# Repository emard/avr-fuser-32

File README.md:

# AVR-Fuser 32

3-in-1 Resurrector programmer for AVR chips

    HVPP: High-Voltage Parallel Programmer
    HVSP: High-Voltage Serial Programmer
    ISP:  In-System Programmer (SPI)

Based on [AVR-Doper](https://www.obdev.at/products/vusb/avrdoper.html)
firmware running on ATMEGA32 in DIP-40 socket.

AVRDUDE compatible, USB powered, onboard 5V->12V converter,
10-pin ISP header, 20-pin HVPP/HVSP header and 
adapter PCB for many popular DIP packages.

Quick mode without PC and avrdude: Pushbutton
erases chip to factory default state.

Complete with firmware, bootloader, kicad schematics and PCB 
for the programmer and sockets adapter.

Supported devices (I tried many but not all of them :)

    ATMEGA 8, 16, 32, 162, 168P, 328P, 16M1, 32M1, 64M1, 8515, 8535
    ATTINY 11, 13, 15, 26, 84, 85, 2313, 4313

# Remark

This is my old project, just uplodaded to github in order
not to get lost, without trying it to compile or open 
since a long time.

May need some fitting for new avr-gcc and kicad 4.x

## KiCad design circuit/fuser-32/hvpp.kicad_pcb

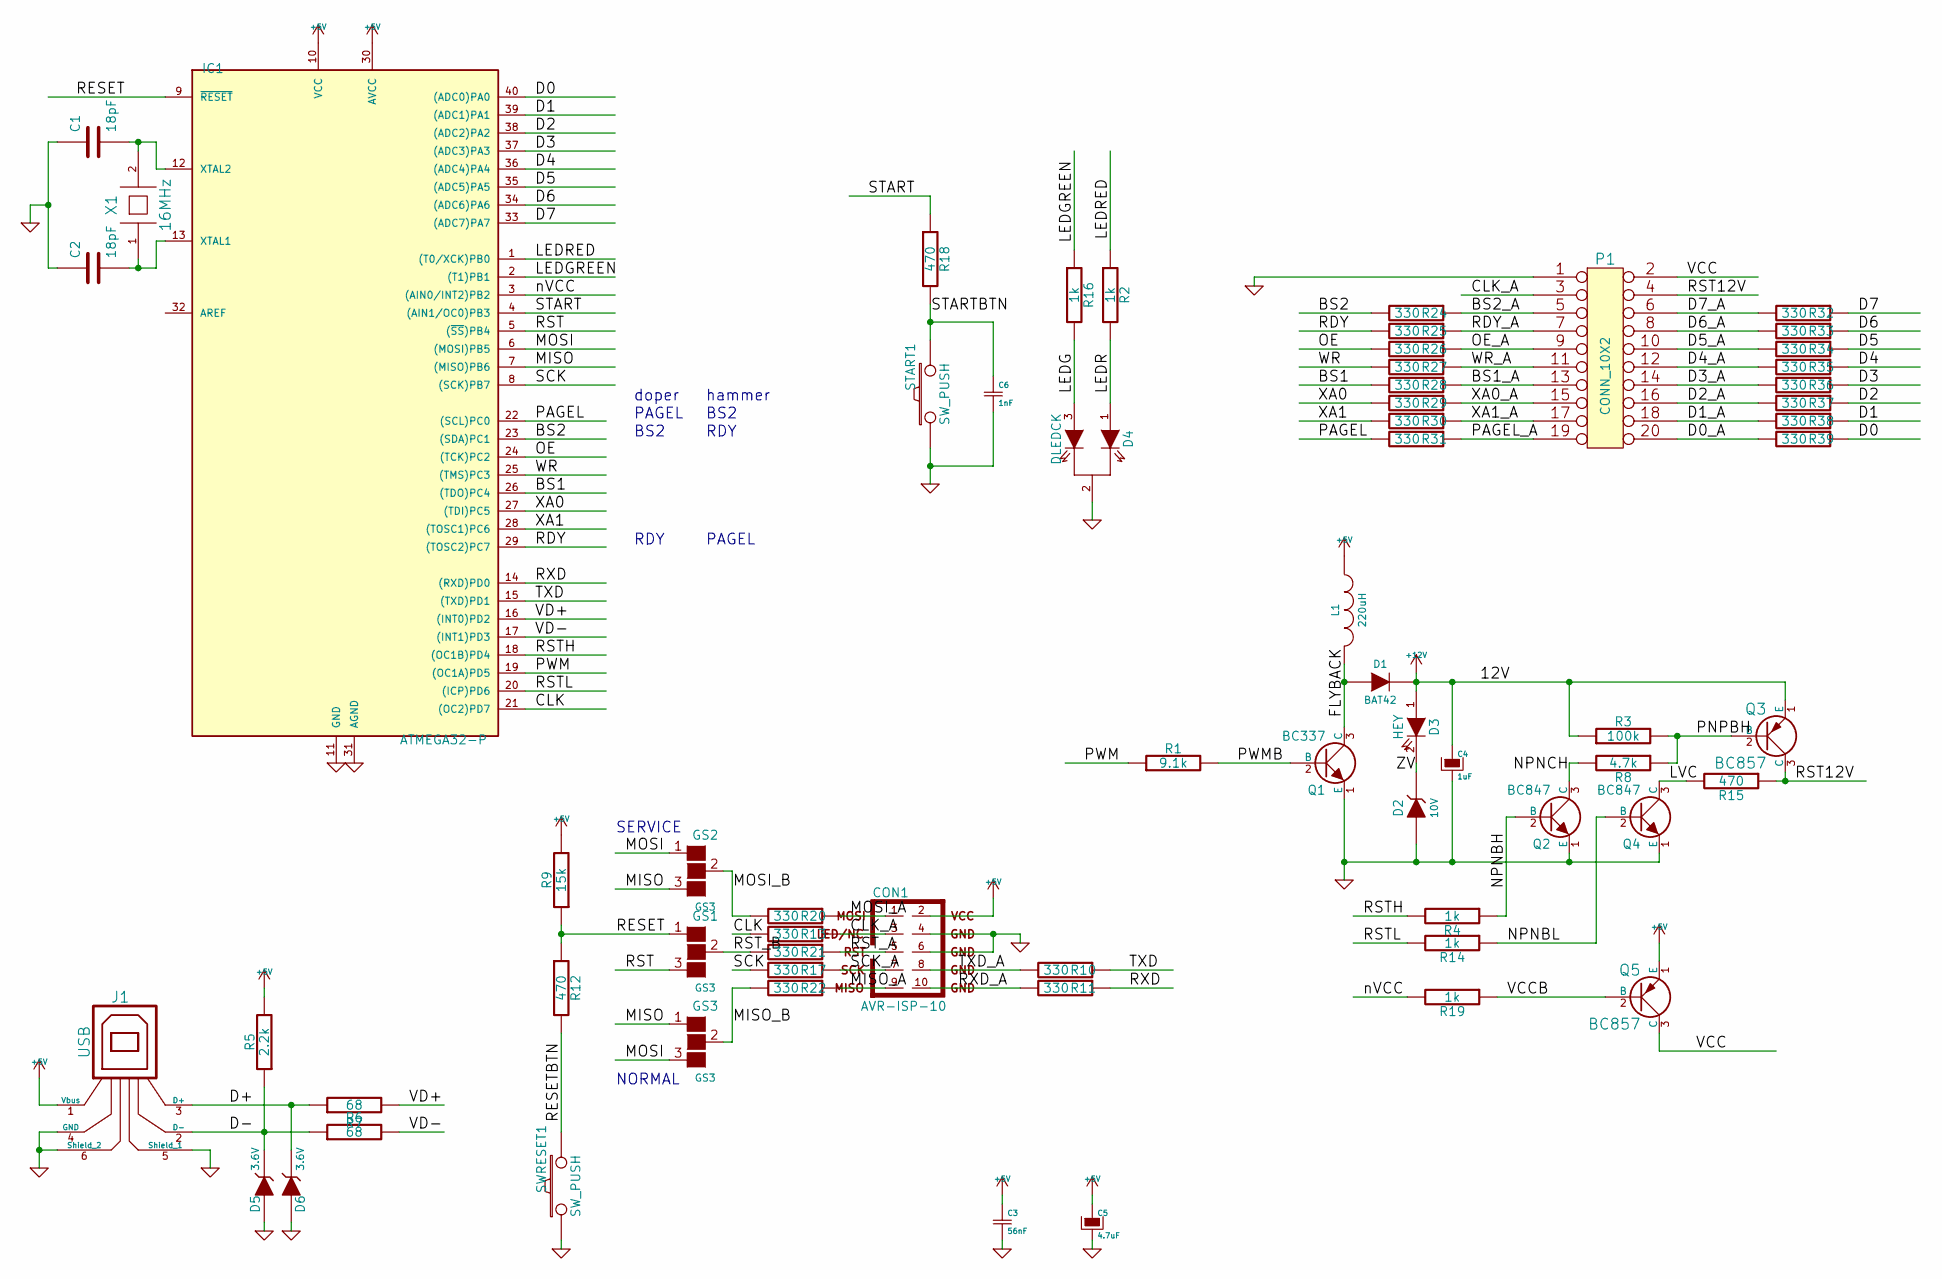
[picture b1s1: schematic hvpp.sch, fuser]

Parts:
C1, C2: 18pF
C3: 56nF
C4: 1uF
C5: 4.7uF
C6: 1nF
CON1: AVR-ISP-10
D1: BAT42
D2: 10V
D3: HEY
D4: DLEDCK
D5, D6: 3.6V
GS1, GS2, GS3: GS3
IC1: ATMEGA32-P; DIL40
J1: USB
L1: 220uH
P1: CONN_10X2
Q1: BC337
Q2, Q4: BC847
Q3, Q5: BC857
R1: 9.1k
R2, R4, R14, R16, R19: 1k
R3: 100k
R5: 2.2k
R6, R7: 68
R8: 4.7k
R9: 15k
R10, R11, R13, R17, R20, R21, R22, R24, R25, R26, R27, R28, R29, R30, R31, R32, R33, R34, R35, R36, R37, R38, R39: 330
R12, R15, R18: 470
START1: SW_PUSH
SWRESET1: SW_PUSH
X1: 16MHz

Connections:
+5V: C3.1, C5.1, CON1.2, IC1.10 (VCC), IC1.30 (AVCC), J1.1 (Vbus), L1.1, Q5.1 (E), R5.2, R9.2
+12V: C4.1, D1.2 (K), D3.1 (A), Q3.1 (E), R3.1
/BS1: IC1.26 ((TDO)PC4), R28.2
/BS1_A: P1.13, R28.1
/BS2: IC1.23 ((SDA)PC1), R24.2
/BS2_A: P1.5, R24.1
/CLK: IC1.21 ((OC2)PD7), R13.2
/CLK_A: CON1.3, P1.3, R13.1
/D0: IC1.40 ((ADC0)PA0), R39.1
/D0_A: P1.20, R39.2
/D1: IC1.39 ((ADC1)PA1), R38.1
/D1_A: P1.18, R38.2
/D2: IC1.38 ((ADC2)PA2), R37.1
/D2_A: P1.16, R37.2
/D3: IC1.37 ((ADC3)PA3), R36.1
/D3_A: P1.14, R36.2
/D4: IC1.36 ((ADC4)PA4), R35.1
/D4_A: P1.12, R35.2
/D5: IC1.35 ((ADC5)PA5), R34.1
/D5_A: P1.10, R34.2
/D6: IC1.34 ((ADC6)PA6), R33.1
/D6_A: P1.8, R33.2
/D7: IC1.33 ((ADC7)PA7), R32.1
/D7_A: P1.6, R32.2
/D+: D6.2 (K), J1.3 (D+), R7.1
/D-: D5.2 (K), J1.2 (D-), R5.1, R6.1
/FLYBACK: D1.1 (A), L1.2, Q1.3 (C)
/LEDG: D4.3 (AGREEN), R16.2
/LEDGREEN: IC1.2 ((T1)PB1), R16.1
/LEDR: D4.1 (ARED), R2.2
/LEDRED: IC1.1 ((T0/XCK)PB0), R2.1
/LVC: Q4.3 (C), R15.2
/MISO: GS2.3 (G3), GS3.1 (G1), IC1.7 ((MISO)PB6)
/MISO_A: CON1.9, R22.1
/MISO_B: GS3.2 (G2), R22.2
/MOSI: GS2.1 (G1), GS3.3 (G3), IC1.6 ((MOSI)PB5)
/MOSI_A: CON1.1, R20.1
/MOSI_B: GS2.2 (G2), R20.2
/NPNBH: Q2.2 (B), R4.1
/NPNBL: Q4.2 (B), R14.1
/NPNCH: Q2.3 (C), R8.2
/OE: IC1.24 ((TCK)PC2), R26.2
/OE_A: P1.9, R26.1
/PAGEL: IC1.22 ((SCL)PC0), R31.2
/PAGEL_A: P1.19, R31.1
/PNPBH: Q3.2 (B), R3.2, R8.1
/PWM: IC1.19 ((OC1A)PD5), R1.1
/PWMB: Q1.2 (B), R1.2
/RDY: IC1.29 ((TOSC2)PC7), R25.2
/RDY_A: P1.7, R25.1
/RESET: GS1.1 (G1), IC1.9 (~RESET), R9.1, R12.1
/RESETBTN: R12.2, SWRESET1.2
/RST: GS1.3 (G3), IC1.5 ((~SS~)PB4)
/RST12V: P1.4, Q3.3 (C), R15.1
/RSTH: IC1.18 ((OC1B)PD4), R4.2
/RSTL: IC1.20 ((ICP)PD6), R14.2
/RST_A: CON1.5, R21.1
/RST_B: GS1.2 (G2), R21.2
/RXD: IC1.14 ((RXD)PD0), R11.1
/RXD_A: CON1.10, R11.2
/SCK: IC1.8 ((SCK)PB7), R17.2
/SCK_A: CON1.7, R17.1
/START: IC1.4 ((AIN1/OC0)PB3), R18.1
/STARTBTN: C6.1, R18.2, START1.2
/TXD: IC1.15 ((TXD)PD1), R10.1
/TXD_A: CON1.8, R10.2
/VCC: P1.2, Q5.3 (C)
/VCCB: Q5.2 (B), R19.1
/VD+: IC1.16 ((INT0)PD2), R7.2
/VD-: IC1.17 ((INT1)PD3), R6.2
/WR: IC1.25 ((TMS)PC3), R27.2
/WR_A: P1.11, R27.1
/XA0: IC1.27 ((TDI)PC5), R29.2
/XA0_A: P1.15, R29.1
/XA1: IC1.28 ((TOSC1)PC6), R30.2
/XA1_A: P1.17, R30.1
/ZV: D2.2 (K), D3.2 (K)
/nVCC: IC1.3 ((AIN0/INT2)PB2), R19.2
GND: C1.1, C2.1, C3.2, C4.2, C5.2, C6.2, CON1.4, CON1.6, D2.1 (A), D4.2 (K), D5.1 (A), D6.1 (A), IC1.11 (GND), IC1.31 (AGND), J1.4 (GND), J1.5 (Shield_1), J1.6 (Shield_2), P1.1, Q1.1 (E), Q2.1 (E), Q4.1 (E), START1.1, SWRESET1.1
unnamed: C1.2, IC1.12 (XTAL2), X1.2
unnamed: C2.2, IC1.13 (XTAL1), X1.1

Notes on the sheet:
doper
SERVICE
NORMAL
PAGEL
RDY
BS2
hammer

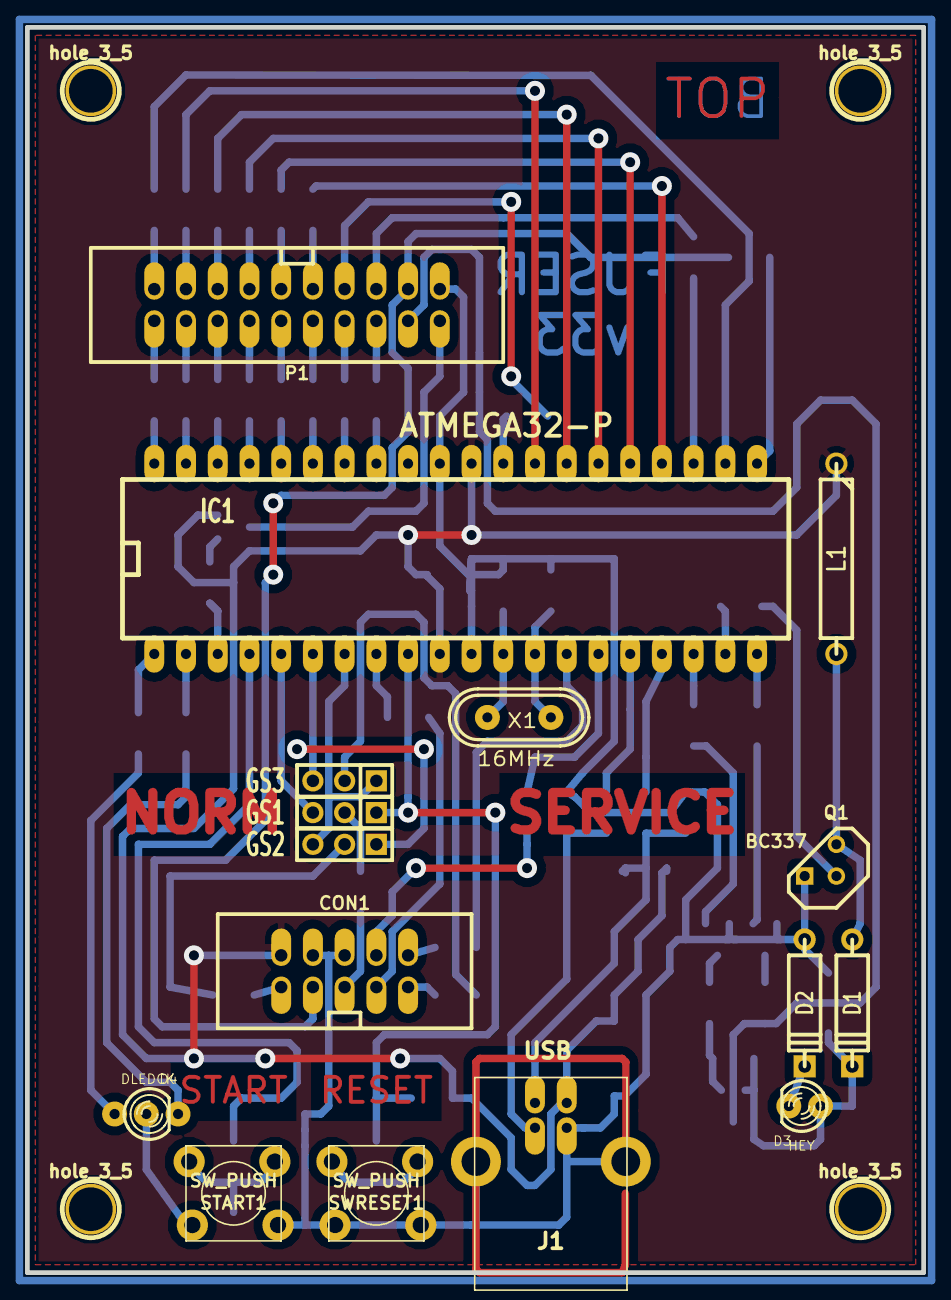
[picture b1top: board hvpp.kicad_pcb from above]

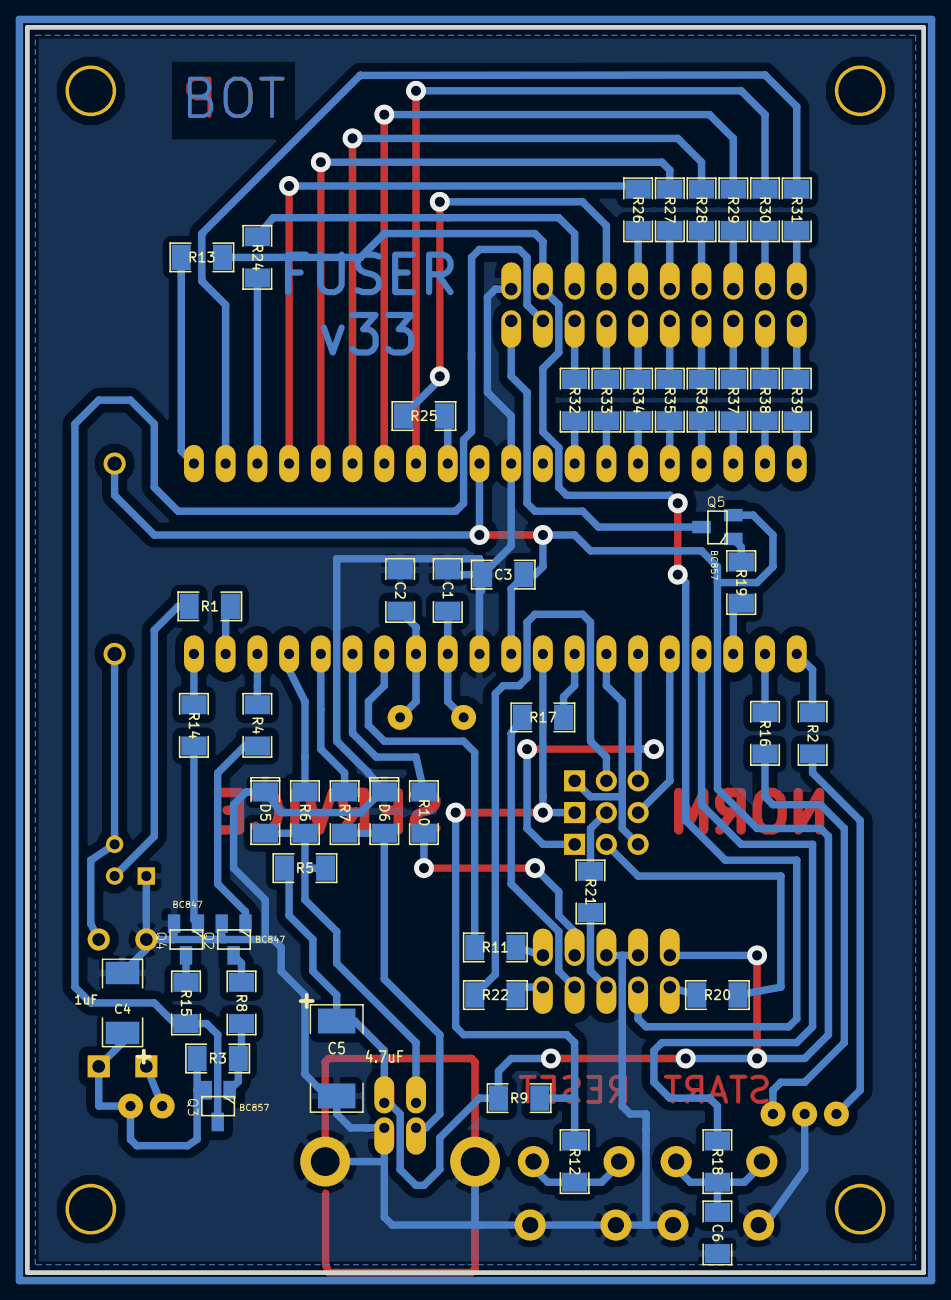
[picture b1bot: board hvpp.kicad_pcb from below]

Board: 2 copper layers, 71.8 x 99.7 mm, 70 parts (50 on the bottom side), 81 nets.

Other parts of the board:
hole_3_5, hole_3_5#2, hole_3_5#3, hole_3_5#4: 3.5mm; hole_3_5

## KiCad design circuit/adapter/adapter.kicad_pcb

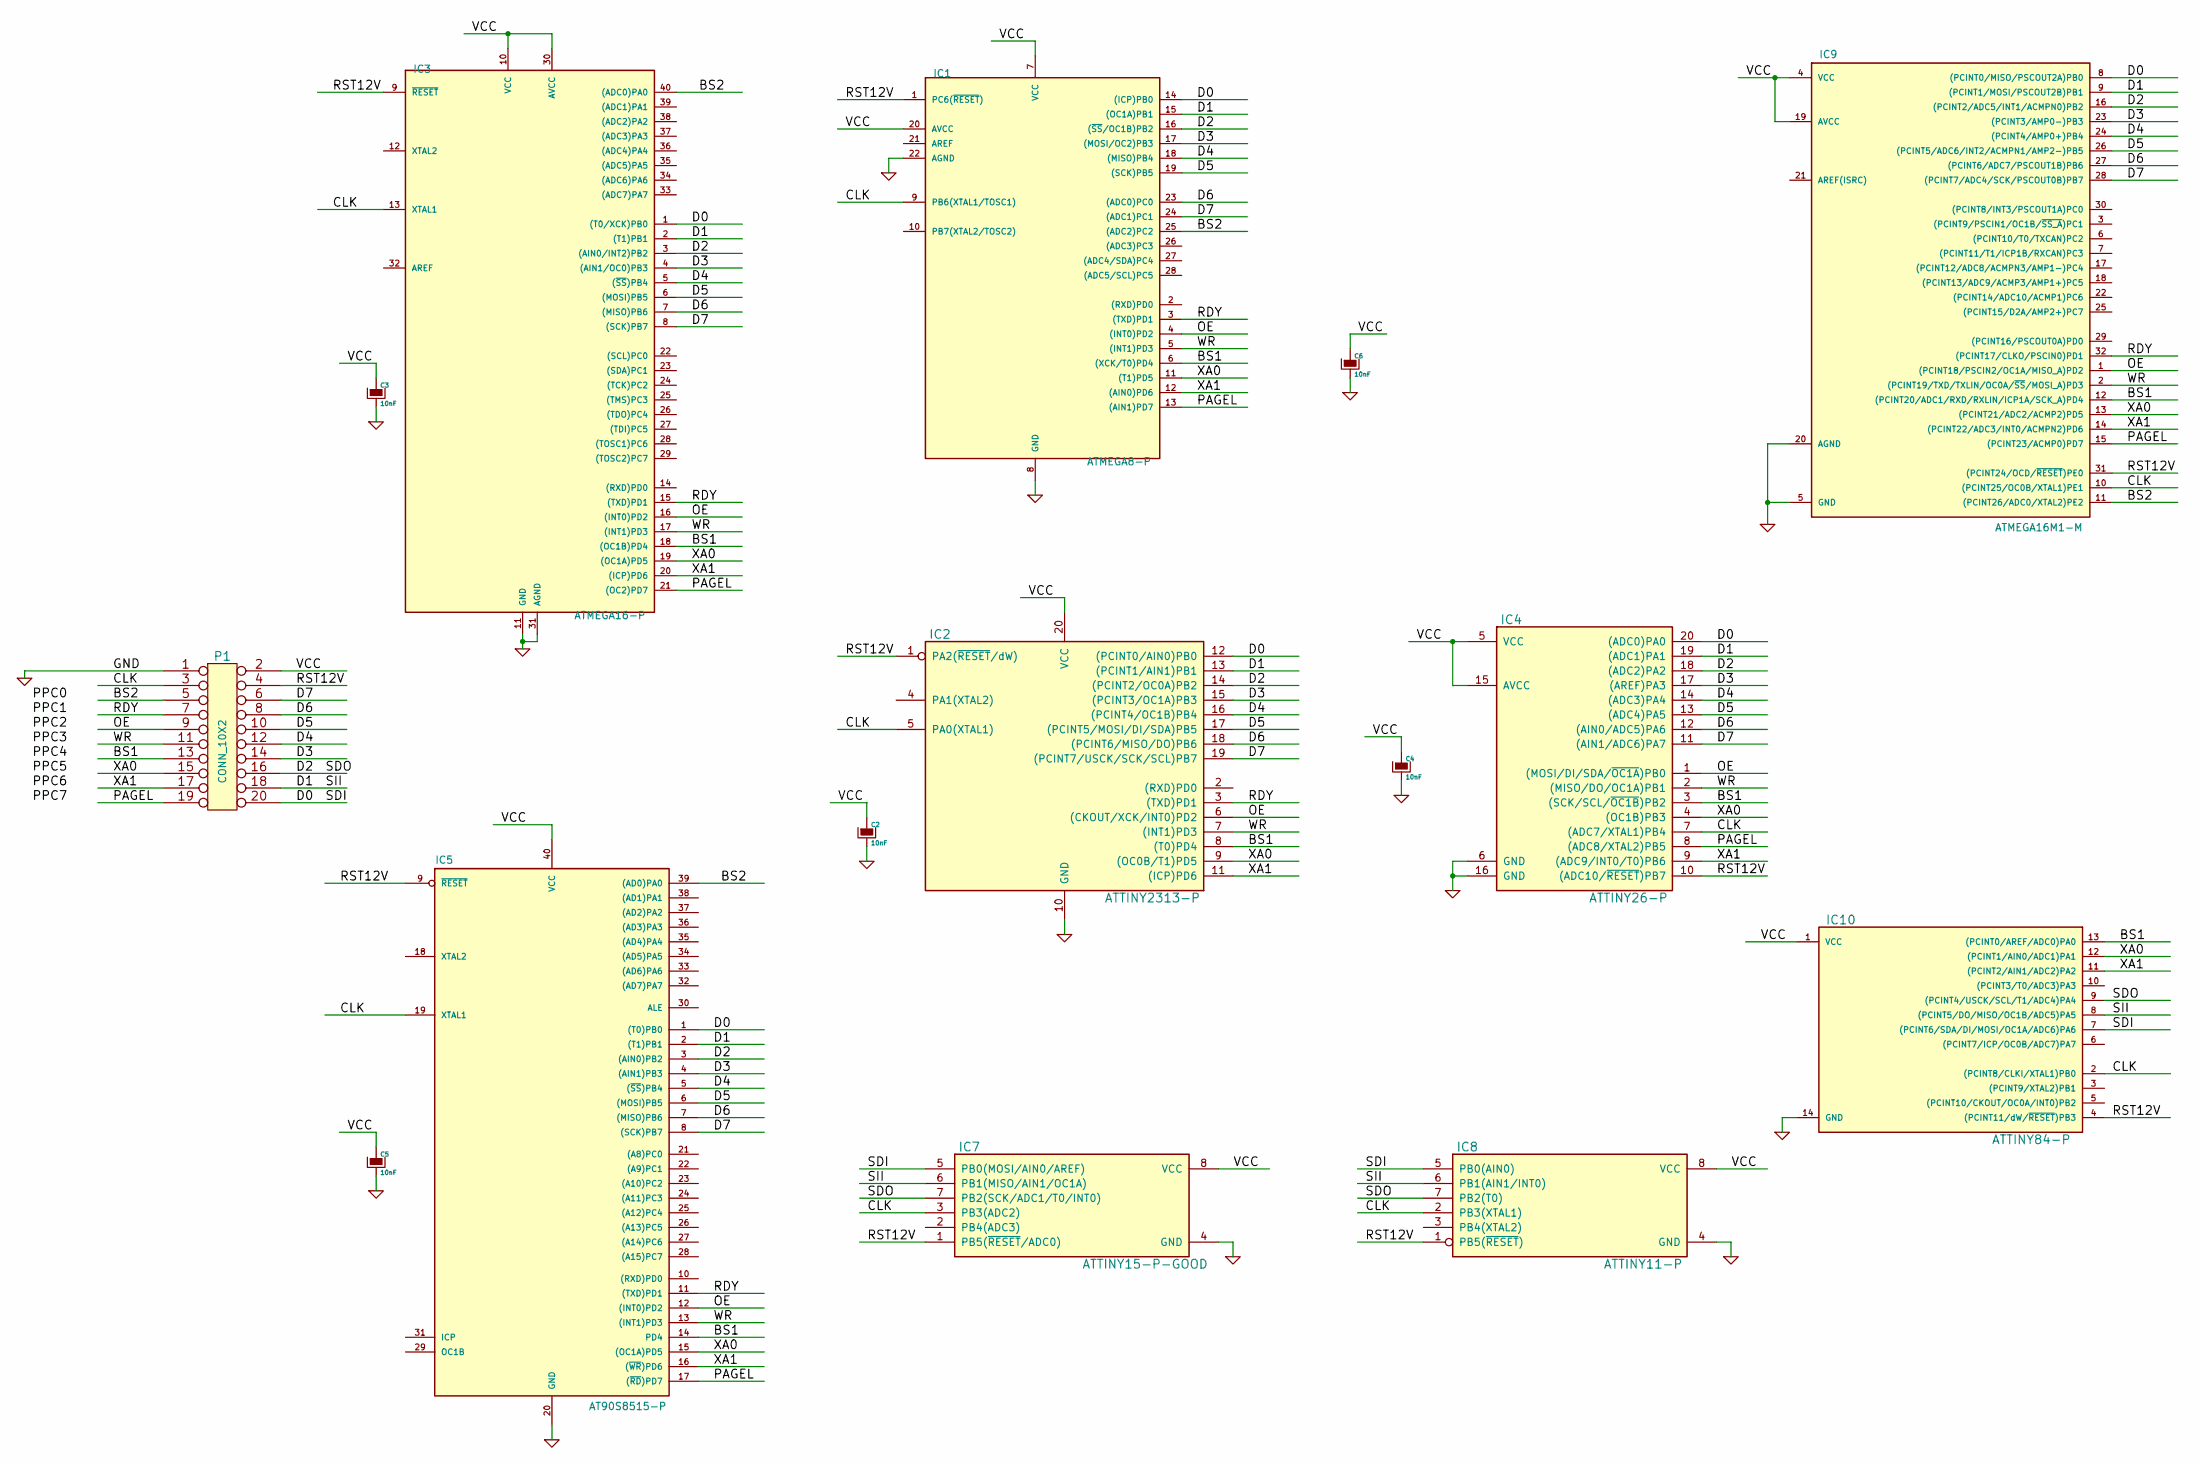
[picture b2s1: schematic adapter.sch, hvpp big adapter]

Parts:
C2, C3, C4, C5, C6: 10nF
IC1: ATMEGA8-P; DIL28
IC2: ATTINY2313-P; DIP20
IC3: ATMEGA16-P; DIL40
IC4: ATTINY26-P; DIP20
IC5: AT90S8515-P; DIL40
IC7: ATTINY15-P-GOOD; DIP8
IC8: ATTINY11-P; DIP8
IC9: ATMEGA16M1-M; QFN32
IC10: ATTINY84-P; DIP14
P1: CONN_10X2

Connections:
/BS1: IC1.6 ((XCK/T0)PD4), IC2.8 ((T0)PD4), IC3.18 ((OC1B)PD4), IC4.3 ((SCK/SCL/~OC1B~)PB2), IC5.14 (PD4), IC9.12 ((PCINT20/ADC1/RXD/RXLIN/ICP1A/SCK_A)PD4), IC10.13 ((PCINT0/AREF/ADC0)PA0), P1.13
/BS2: IC1.25 ((ADC2)PC2), IC3.40 ((ADC0)PA0), IC5.39 ((AD0)PA0), IC9.11 ((PCINT26/ADC0/XTAL2)PE2), P1.5
/CLK: IC1.9 (PB6(XTAL1/TOSC1)), IC2.5 (PA0(XTAL1)), IC3.13 (XTAL1), IC4.7 ((ADC7/XTAL1)PB4), IC5.19 (XTAL1), IC7.3 (PB3(ADC2)), IC8.2 (PB3(XTAL1)), IC9.10 ((PCINT25/OC0B/XTAL1)PE1), IC10.2 ((PCINT8/CLKI/XTAL1)PB0), P1.3
/D0: IC1.14 ((ICP)PB0), IC2.12 ((PCINT0/AIN0)PB0), IC3.1 ((T0/XCK)PB0), IC4.20 ((ADC0)PA0), IC5.1 ((T0)PB0), IC7.5 (PB0(MOSI/AIN0/AREF)), IC8.5 (PB0(AIN0)), IC9.8 ((PCINT0/MISO/PSCOUT2A)PB0), IC10.7 ((PCINT6/SDA/DI/MOSI/OC1A/ADC6)PA6), P1.20
/D1: IC1.15 ((OC1A)PB1), IC2.13 ((PCINT1/AIN1)PB1), IC3.2 ((T1)PB1), IC4.19 ((ADC1)PA1), IC5.2 ((T1)PB1), IC7.6 (PB1(MISO/AIN1/OC1A)), IC8.6 (PB1(AIN1/INT0)), IC9.9 ((PCINT1/MOSI/PSCOUT2B)PB1), IC10.8 ((PCINT5/DO/MISO/OC1B/ADC5)PA5), P1.18
/D2: IC1.16 ((~SS~/OC1B)PB2), IC2.14 ((PCINT2/OC0A)PB2), IC3.3 ((AIN0/INT2)PB2), IC4.18 ((ADC2)PA2), IC5.3 ((AIN0)PB2), IC7.7 (PB2(SCK/ADC1/T0/INT0)), IC8.7 (PB2(T0)), IC9.16 ((PCINT2/ADC5/INT1/ACMPN0)PB2), IC10.9 ((PCINT4/USCK/SCL/T1/ADC4)PA4), P1.16
/D3: IC1.17 ((MOSI/OC2)PB3), IC2.15 ((PCINT3/OC1A)PB3), IC3.4 ((AIN1/OC0)PB3), IC4.17 ((AREF)PA3), IC5.4 ((AIN1)PB3), IC9.23 ((PCINT3/AMP0-)PB3), P1.14
/D4: IC1.18 ((MISO)PB4), IC2.16 ((PCINT4/OC1B)PB4), IC3.5 ((~SS~)PB4), IC4.14 ((ADC3)PA4), IC5.5 ((~SS~)PB4), IC9.24 ((PCINT4/AMP0+)PB4), P1.12
/D5: IC1.19 ((SCK)PB5), IC2.17 ((PCINT5/MOSI/DI/SDA)PB5), IC3.6 ((MOSI)PB5), IC4.13 ((ADC4)PA5), IC5.6 ((MOSI)PB5), IC9.26 ((PCINT5/ADC6/INT2/ACMPN1/AMP2-)PB5), P1.10
/D6: IC1.23 ((ADC0)PC0), IC2.18 ((PCINT6/MISO/DO)PB6), IC3.7 ((MISO)PB6), IC4.12 ((AIN0/ADC5)PA6), IC5.7 ((MISO)PB6), IC9.27 ((PCINT6/ADC7/PSCOUT1B)PB6), P1.8
/D7: IC1.24 ((ADC1)PC1), IC2.19 ((PCINT7/USCK/SCK/SCL)PB7), IC3.8 ((SCK)PB7), IC4.11 ((AIN1/ADC6)PA7), IC5.8 ((SCK)PB7), IC9.28 ((PCINT7/ADC4/SCK/PSCOUT0B)PB7), P1.6
/OE: IC1.4 ((INT0)PD2), IC2.6 ((CKOUT/XCK/INT0)PD2), IC3.16 ((INT0)PD2), IC4.1 ((MOSI/DI/SDA/~OC1A~)PB0), IC5.12 ((INT0)PD2), IC9.1 ((PCINT18/PSCIN2/OC1A/MISO_A)PD2), P1.9
/PAGEL: IC1.13 ((AIN1)PD7), IC3.21 ((OC2)PD7), IC4.8 ((ADC8/XTAL2)PB5), IC5.17 ((~RD~)PD7), IC9.15 ((PCINT23/ACMP0)PD7), P1.19
/RDY: IC1.3 ((TXD)PD1), IC2.3 ((TXD)PD1), IC3.15 ((TXD)PD1), IC5.11 ((TXD)PD1), IC9.32 ((PCINT17/CLKO/PSCIN0)PD1), P1.7
/RST12V: IC1.1 (PC6(~RESET~)), IC2.1 (PA2(~RESET~/dW)), IC3.9 (~RESET), IC4.10 ((ADC10/~RESET~)PB7), IC5.9 (~RESET), IC7.1 (PB5(~RESET~/ADC0)), IC8.1 (PB5(~RESET~)), IC9.31 ((PCINT24/OCD/~RESET~)PE0), IC10.4 ((PCINT11/dW/~RESET~)PB3), P1.4
/VCC: C2.1, C3.1, C4.1, C5.1, C6.1, IC1.7 (VCC), IC1.20 (AVCC), IC2.20 (VCC), IC3.10 (VCC), IC3.30 (AVCC), IC4.5 (VCC), IC4.15 (AVCC), IC5.40 (VCC), IC7.8 (VCC), IC8.8 (VCC), IC9.4 (VCC), IC9.19 (AVCC), IC10.1 (VCC), P1.2
/WR: IC1.5 ((INT1)PD3), IC2.7 ((INT1)PD3), IC3.17 ((INT1)PD3), IC4.2 ((MISO/DO/OC1A)PB1), IC5.13 ((INT1)PD3), IC9.2 ((PCINT19/TXD/TXLIN/OC0A/~SS~/MOSI_A)PD3), P1.11
/XA0: IC1.11 ((T1)PD5), IC2.9 ((OC0B/T1)PD5), IC3.19 ((OC1A)PD5), IC4.4 ((OC1B)PB3), IC5.15 ((OC1A)PD5), IC9.13 ((PCINT21/ADC2/ACMP2)PD5), IC10.12 ((PCINT1/AIN0/ADC1)PA1), P1.15
/XA1: IC1.12 ((AIN0)PD6), IC2.11 ((ICP)PD6), IC3.20 ((ICP)PD6), IC4.9 ((ADC9/INT0/T0)PB6), IC5.16 ((~WR~)PD6), IC9.14 ((PCINT22/ADC3/INT0/ACMPN2)PD6), IC10.11 ((PCINT2/AIN1/ADC2)PA2), P1.17
GND: C2.2, C3.2, C4.2, C5.2, C6.2, IC1.8 (GND), IC1.22 (AGND), IC2.10 (GND), IC3.11 (GND), IC3.31 (AGND), IC4.6 (GND), IC4.16 (GND), IC5.20 (GND), IC7.4 (GND), IC8.4 (GND), IC9.5 (GND), IC9.20 (AGND), IC10.14 (GND), P1.1

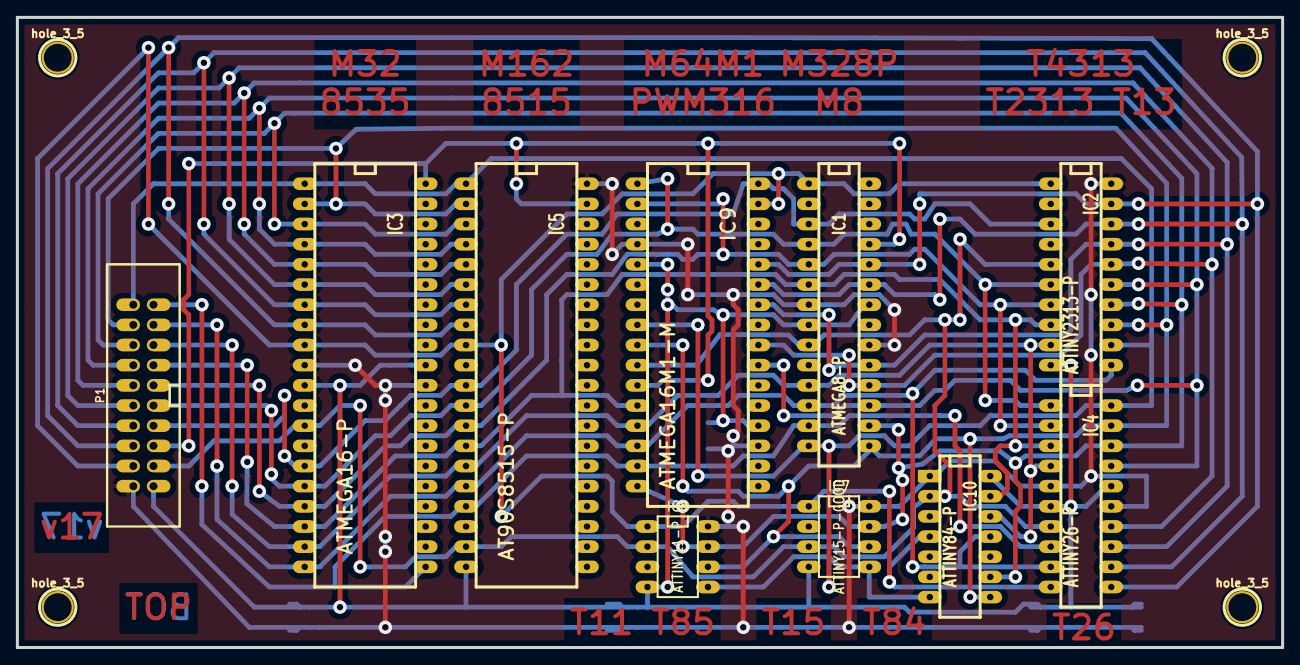
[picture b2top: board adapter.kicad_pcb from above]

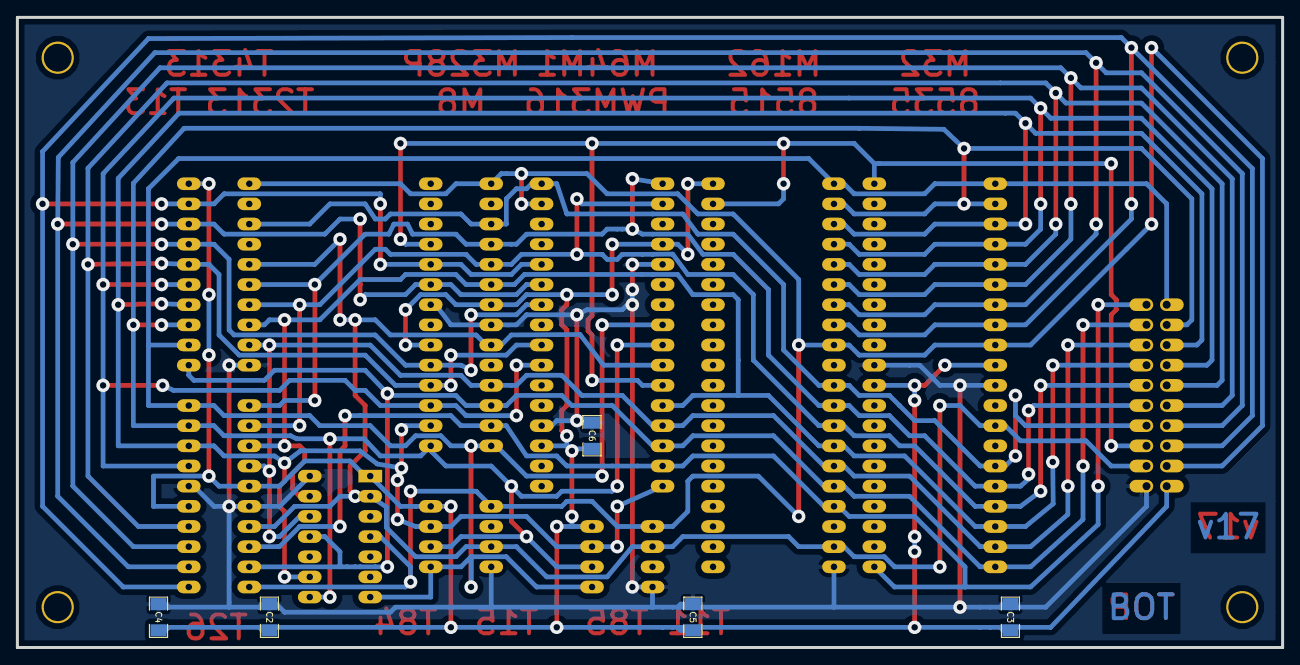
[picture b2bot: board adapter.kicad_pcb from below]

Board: 2 copper layers, 159.4 x 79.4 mm, 19 parts (5 on the bottom side), 20 nets.

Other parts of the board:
hole_3_5, hole_3_5#2, hole_3_5#3, hole_3_5#4: 3.5mm; hole_3_5

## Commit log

2017-05-24 uploading my old repository
2017-05-24 gitignore files for kicad
2017-05-24 adapter PCB: open with Kicad 4.x and saving
2017-05-24 fuser-32 programmer PCB: open with kicad 4.x and saving
2017-05-24 readme update (supported chips)
2017-05-24 readme update
2017-05-24 fixing some DRC (text over copper traces) fuser32: gerbers update, preparation for seeedstudio production
2017-05-24 adapter bump version to v18
2017-05-24 adapter gerbers update, prepararion for seeedstudio production
